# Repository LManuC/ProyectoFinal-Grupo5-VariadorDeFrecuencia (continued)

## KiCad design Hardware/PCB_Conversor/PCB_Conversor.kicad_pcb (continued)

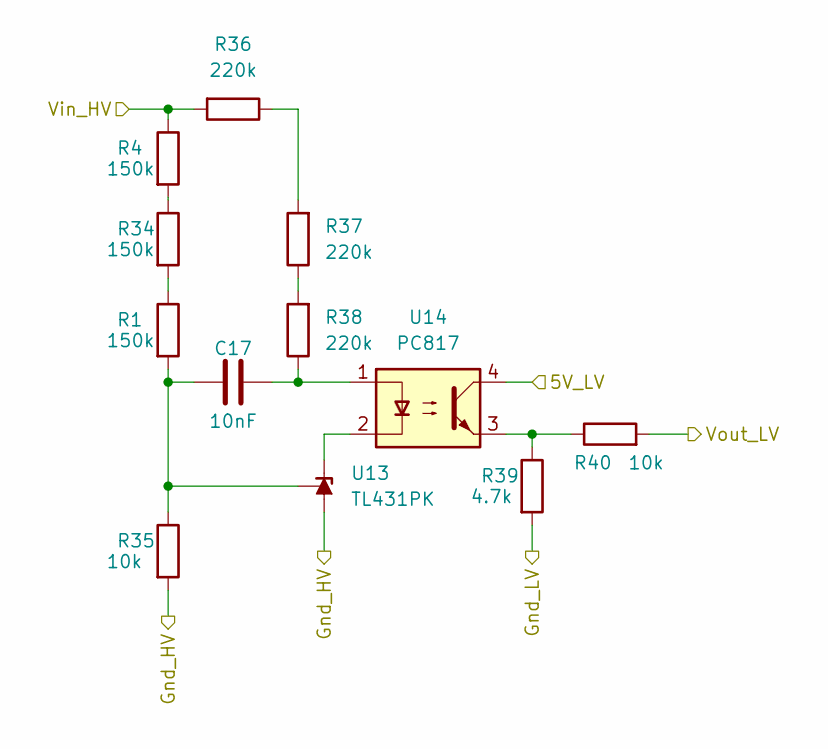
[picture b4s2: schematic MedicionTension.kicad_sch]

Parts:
C17: 10nF; C_0603_1608Metric_Pad1.08x0.95mm_HandSolder
R1, R4, R34: 150k; R_0603_1608Metric_Pad0.98x0.95mm_HandSolder
R35, R40: 10k; R_0603_1608Metric_Pad0.98x0.95mm_HandSolder
R36, R37, R38: 220k; R_0603_1608Metric_Pad0.98x0.95mm_HandSolder
R39: 4.7k; R_0603_1608Metric_Pad0.98x0.95mm_HandSolder
U13: TL431PK; SOT-89-3_Handsoldering
U14: PC817; DIP-4_W7.62mm_SMDSocket_SmallPads

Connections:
/Conversor/Gnd_Inv: R35.2, U13.2 (A); also elsewhere on the board
GND_Cnv: R39.2; also elsewhere on the board
unnamed: C17.2, R38.1, U14.1
unnamed: R1.1, R34.2
unnamed: R4.2, R34.1
unnamed: R36.1, R37.2
unnamed: R37.1, R38.2
unnamed: R39.1, R40.1, U14.3
unnamed: U13.3 (K), U14.2
unnamed: C17.1, R1.2, R35.1, U13.1 (REF)
V_HVBus: R4.1, R36.2; also elsewhere on the board
Vref_5V: U14.4; also elsewhere on the board
Vsens_HVDCBus: R40.2; also elsewhere on the board

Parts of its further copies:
C18: 10nF; C_0603_1608Metric_Pad1.08x0.95mm_HandSolder
R3, R5, R41: 150k; R_0603_1608Metric_Pad0.98x0.95mm_HandSolder
R42, R47: 10k; R_0603_1608Metric_Pad0.98x0.95mm_HandSolder
R43, R44, R45: 220k; R_0603_1608Metric_Pad0.98x0.95mm_HandSolder
R46: 4.7k; R_0603_1608Metric_Pad0.98x0.95mm_HandSolder
U15: TL431PK; SOT-89-3_Handsoldering
U16: PC817; DIP-4_W7.62mm_SMDSocket_SmallPads

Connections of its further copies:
3V3_HMI: U16.4; also elsewhere on the board
/Conversor/Gnd_Inv: R42.2, U15.2 (A); also elsewhere on the board
GND_Cnv: R46.2; also elsewhere on the board
unnamed: C18.2, R45.1, U16.1
unnamed: R3.1, R41.2
unnamed: R5.2, R41.1
unnamed: R43.1, R44.2
unnamed: R44.1, R45.2
unnamed: R46.1, R47.1, U16.3
unnamed: U15.3 (K), U16.2
unnamed: C18.1, R3.2, R42.1, U15.1 (REF)
V_HVBus: R5.1, R43.2; also elsewhere on the board
Vsens_HV_HMI: R47.2; also elsewhere on the board

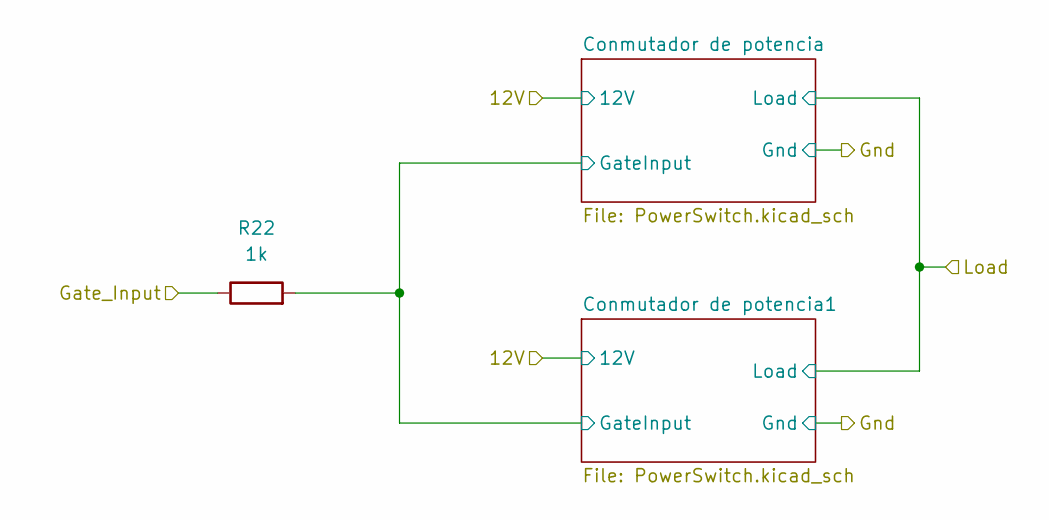
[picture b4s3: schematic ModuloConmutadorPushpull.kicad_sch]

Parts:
R22: 1k; R_0603_1608Metric_Pad0.98x0.95mm_HandSolder

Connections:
/Conversor/Modulo conmutador pushpull/Conmutador de potencia/GateInput: R22.2; also elsewhere on the board
Gate_Input_B: R22.1; also elsewhere on the board

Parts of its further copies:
R24: 1k; R_0603_1608Metric_Pad0.98x0.95mm_HandSolder

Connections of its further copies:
/Conversor/Modulo conmutador pushpull1/Conmutador de potencia/GateInput: R24.2; also elsewhere on the board
Gate_Input_A: R24.1; also elsewhere on the board

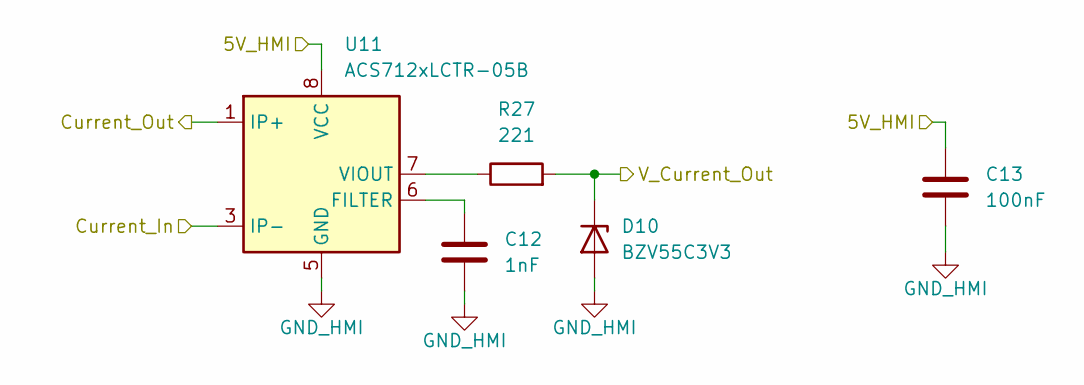
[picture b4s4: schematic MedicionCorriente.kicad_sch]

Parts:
C12: 1nF; C_0603_1608Metric_Pad1.08x0.95mm_HandSolder
C13: 100nF; C_0603_1608Metric_Pad1.08x0.95mm_HandSolder
D10: BZV55C3V3; D_MiniMELF_Handsoldering
R27: 221; R_0603_1608Metric_Pad0.98x0.95mm_HandSolder
U11: ACS712xLCTR-05B; SOIC-8_3.9x4.9mm_P1.27mm

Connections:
5V_HMI: C13.1, U11.8 (VCC); also elsewhere on the board
/Conversor/Medición corriente/Current_In: U11.3 (IP-), U11.4 (IP-); also elsewhere on the board
GND_HMI: C12.2, C13.2, D10.2 (A), U11.5 (GND); also elsewhere on the board
unnamed: C12.1, U11.6 (FILTER)
unnamed: R27.1, U11.7 (VIOUT)
VSens_Corriente: D10.1 (K), R27.2; also elsewhere on the board
V_HVBus: U11.1 (IP+), U11.2 (IP+); also elsewhere on the board

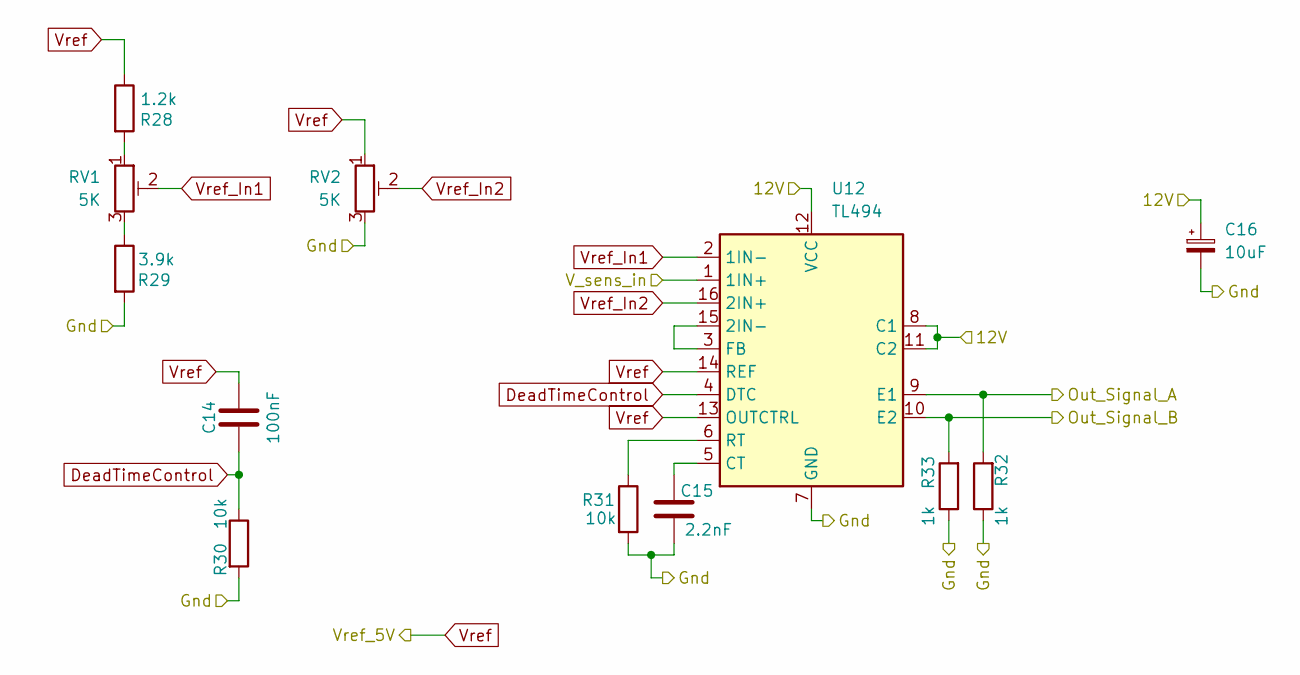
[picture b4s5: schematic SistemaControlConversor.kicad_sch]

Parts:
C14: 100nF; C_0603_1608Metric_Pad1.08x0.95mm_HandSolder
C15: 2.2nF; C_0603_1608Metric_Pad1.08x0.95mm_HandSolder
C16: 10uF; CP_Elec_4x5.4
R28: 1.2k; R_0603_1608Metric_Pad0.98x0.95mm_HandSolder
R29: 3.9k; R_0603_1608Metric_Pad0.98x0.95mm_HandSolder
R30, R31: 10k; R_0603_1608Metric_Pad0.98x0.95mm_HandSolder
R32, R33: 1k; R_0603_1608Metric_Pad0.98x0.95mm_HandSolder
RV1, RV2: 5K; Potentiometer_Bourns_3314S_Horizontal
U12: TL494; SOIC-16_3.9x9.9mm_P1.27mm

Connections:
12V_Cnv: C16.1, U12.8 (C1), U12.11 (C2), U12.12 (VCC); also elsewhere on the board
DeadTimeControl: C14.1, R30.1, U12.4 (DTC)
GND_Cnv: C15.1, C16.2, R29.2, R30.2, R31.2, R32.1, R33.1, RV2.3, U12.7 (GND); also elsewhere on the board
Gate_Input_A: R32.2, U12.9 (E1); also elsewhere on the board
Gate_Input_B: R33.2, U12.10 (E2); also elsewhere on the board
unnamed: R28.2, RV1.1
unnamed: R29.1, RV1.3
unnamed: U12.3 (FB), U12.15 (2IN-)
unnamed: C15.2, U12.5 (CT)
unnamed: R31.1, U12.6 (RT)
Vref_5V: C14.2, R28.1, RV2.1, U12.13 (OUTCTRL), U12.14 (REF); also elsewhere on the board
Vref_In1: RV1.2, U12.2 (1IN-)
Vref_In2: RV2.2, U12.16 (2IN+)
Vsens_HVDCBus: U12.1 (1IN+); also elsewhere on the board

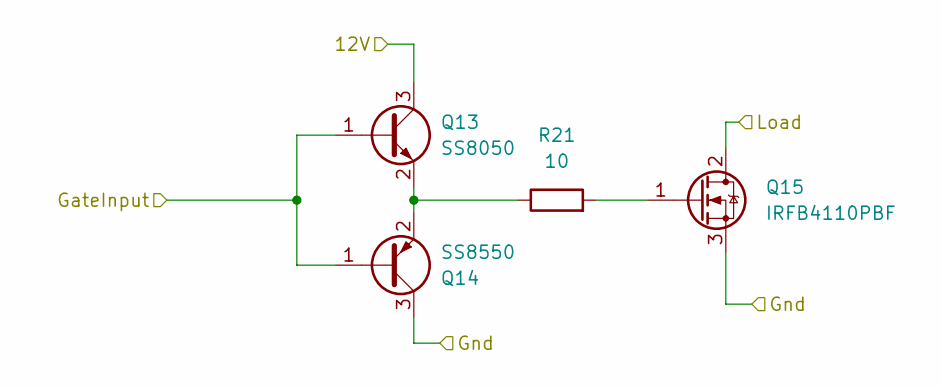
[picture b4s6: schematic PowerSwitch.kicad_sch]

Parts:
Q13: SS8050; SOT-23
Q14: SS8550; SOT-23
Q15: IRFB4110PBF; TO-220-3_Horizontal_TabUp
R21: 10; R_0603_1608Metric_Pad0.98x0.95mm_HandSolder

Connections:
12V_Cnv: Q13.3 (C); also elsewhere on the board
/Conversor/Modulo conmutador pushpull/Conmutador de potencia/GateInput: Q13.1 (B), Q14.1 (B); also elsewhere on the board
/Conversor/Modulo conmutador pushpull/Load: Q15.2 (D); also elsewhere on the board
GND_Cnv: Q14.3 (C), Q15.3 (S); also elsewhere on the board
unnamed: Q13.2 (E), Q14.2 (E), R21.1
unnamed: Q15.1 (G), R21.2

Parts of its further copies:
Q16, Q19, Q22: SS8050; SOT-23
Q17, Q20, Q23: SS8550; SOT-23
Q18, Q21, Q24: IRFB4110PBF; TO-220-3_Horizontal_TabUp
R23, R25, R26: 10; R_0603_1608Metric_Pad0.98x0.95mm_HandSolder

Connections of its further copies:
12V_Cnv: Q16.3 (C), Q19.3 (C), Q22.3 (C); also elsewhere on the board
/Conversor/Modulo conmutador pushpull1/Conmutador de potencia/GateInput: Q19.1 (B), Q20.1 (B), Q22.1 (B), Q23.1 (B); also elsewhere on the board
/Conversor/Modulo conmutador pushpull1/Load: Q21.2 (D), Q24.2 (D); also elsewhere on the board
/Conversor/Modulo conmutador pushpull/Conmutador de potencia/GateInput: Q16.1 (B), Q17.1 (B); also elsewhere on the board
/Conversor/Modulo conmutador pushpull/Load: Q18.2 (D); also elsewhere on the board
GND_Cnv: Q17.3 (C), Q18.3 (S), Q20.3 (C), Q21.3 (S), Q23.3 (C), Q24.3 (S); also elsewhere on the board
unnamed: Q16.2 (E), Q17.2 (E), R23.1
unnamed: Q18.1 (G), R23.2
unnamed: Q19.2 (E), Q20.2 (E), R25.1
unnamed: Q21.1 (G), R25.2
unnamed: Q22.2 (E), Q23.2 (E), R26.1
unnamed: Q24.1 (G), R26.2

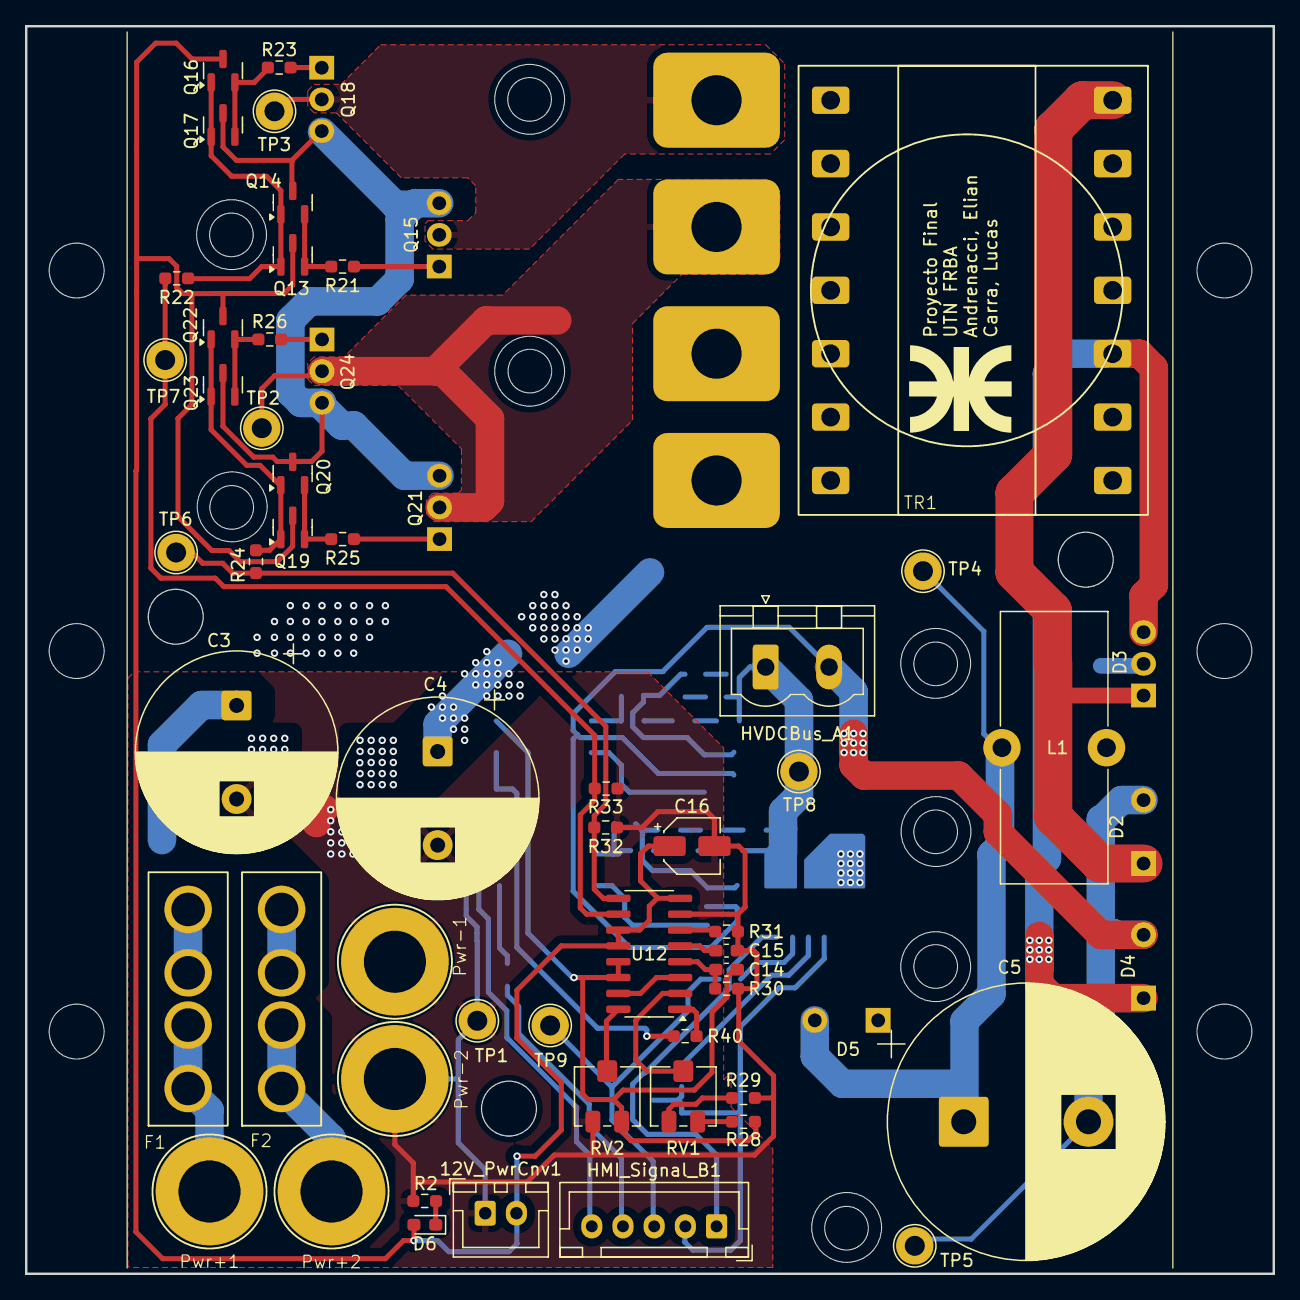
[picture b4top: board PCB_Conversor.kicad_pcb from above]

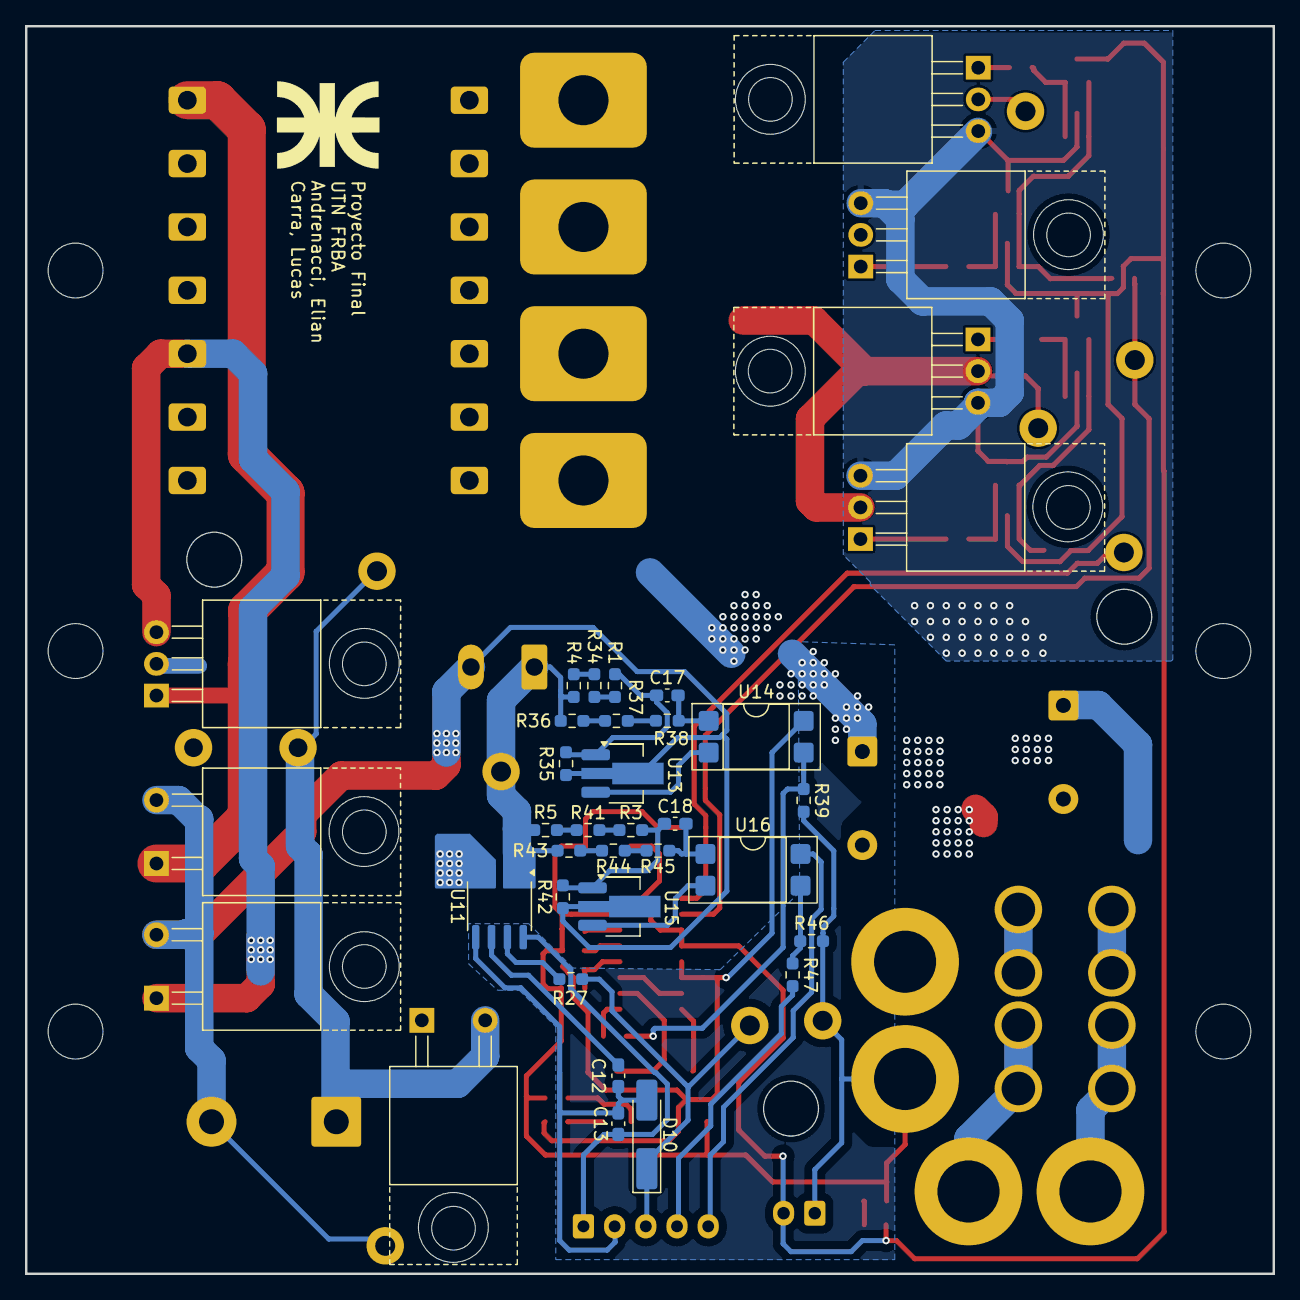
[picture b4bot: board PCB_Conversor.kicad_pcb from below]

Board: 2 copper layers, 100.0 x 100.0 mm, 88 parts (36 on the bottom side), 61 nets.

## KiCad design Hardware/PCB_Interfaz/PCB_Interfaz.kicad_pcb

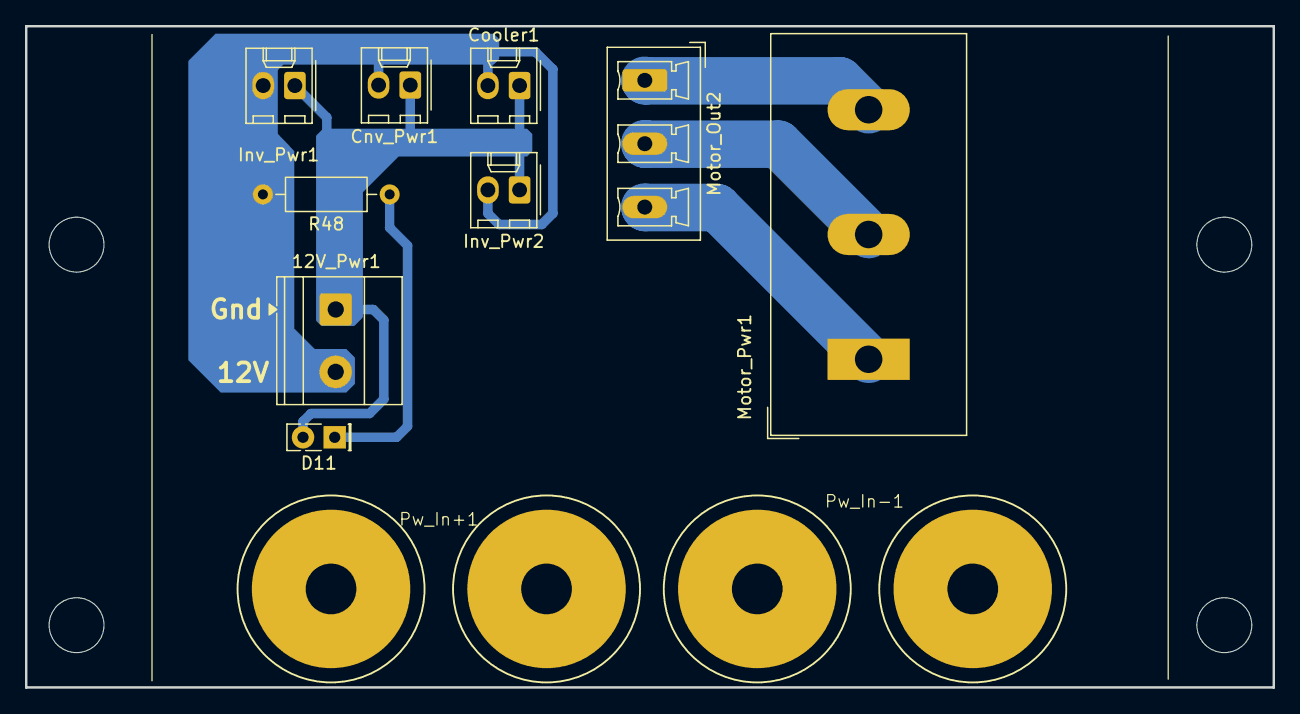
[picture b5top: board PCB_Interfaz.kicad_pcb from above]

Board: 2 copper layers, 100.0 x 53.0 mm, 11 parts (0 on the bottom side), 6 nets.

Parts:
12V_Pwr1: Screw_Terminal_01x02; TerminalBlock_Phoenix_MKDS-1,5-2_1x02_P5.00mm_Horizontal
Cnv_Pwr1: Conn_01x02; Molex_KK-254_AE-6410-02A_1x02_P2.54mm_Vertical
Cooler1: Conn_01x02; Molex_KK-254_AE-6410-02A_1x02_P2.54mm_Vertical
D11: LED_Green; LED_Rectangular_W5.0mm_H2.0mm
Inv_Pwr1, Inv_Pwr2: Conn_01x02; Molex_KK-254_AE-6410-02A_1x02_P2.54mm_Vertical
Motor_Out2: Conn_01x03; PhoenixContact_MCV_1,5_3-G-5.08_1x03_P5.08mm_Vertical
Motor_Pwr1: Screw_Terminal_01x03; TerminalBlock_Dinkle_DT-55-B01X-03_P10.00mm
Pw_In+1: Conn_01x02; BananaSocket - 2P - 4mm
Pw_In-1: Conn_01x02; BananaSocket - 2P - 4mm
R48: 1.2k; R_Axial_DIN0207_L6.3mm_D2.5mm_P10.16mm_Horizontal

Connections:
/Interfaz de conexión/12V_Cnv: 12V_Pwr1.1, Cnv_Pwr1.1, Cooler1.1, D11.2 (A), Inv_Pwr1.1, Inv_Pwr2.1
/Interfaz de conexión/Gnd_Cnv: 12V_Pwr1.2, Cnv_Pwr1.2, Cooler1.2, Inv_Pwr1.2, Inv_Pwr2.2, R48.2
unnamed: D11.1 (K), R48.1
unnamed: Motor_Out2.1, Motor_Pwr1.3
unnamed: Motor_Out2.2, Motor_Pwr1.2
unnamed: Motor_Out2.3, Motor_Pwr1.1

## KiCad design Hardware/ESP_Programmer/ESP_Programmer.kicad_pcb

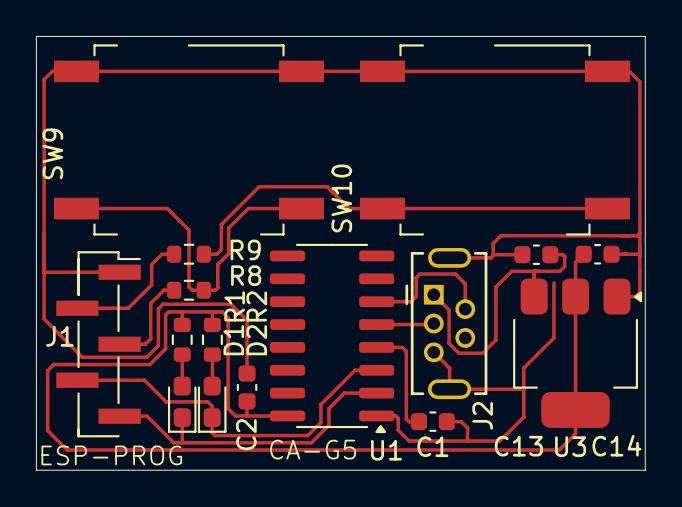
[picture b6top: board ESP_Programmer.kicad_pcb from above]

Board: 2 copper layers, 33.8 x 24.1 mm, 16 parts (0 on the bottom side), 14 nets.

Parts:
C1, C2: 1nF; C_0603_1608Metric
C13, C14: 1uF; C_0603_1608Metric
D1, D2: LED; LED_0603_1608Metric_Pad1.05x0.95mm_HandSolder
J1: Conn_01x05_Pin; PinHeader_1x05_P2.00mm_Vertical_SMD_Pin1Right
J2: USB_OTG; USB_Mini-B_Tensility_54-00023_Vertical
R1, R2, R8, R9: 221; R_0603_1608Metric
SW9, SW10: SW_MEC_5E; SW_MEC_5GSH9
U1: CH340C; SOIC-16_3.9x9.9mm_P1.27mm
U3: AMS1117-3.3; SOT-223-3_TabPin2

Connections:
+3.3V: C2.1, C14.1, R1.1, R2.1, U1.16 (VCC), U3.2 (VO)
+5V: C13.1, J2.1 (VBUS), U3.3 (VI)
/BOOT_prog: J1.2, R9.1
/ENABLE: J1.3, R8.1
/Rx: D2.1 (K), J1.4, U1.3 (RXD)
/Tx: D1.1 (K), J1.5, U1.2 (TXD)
GND: C1.1, C2.2, C13.2, C14.2, J1.1, J2.5 (GND), J2.6 (Shield), SW9.1, SW9.2, SW10.1, SW10.2, U1.1 (GND), U3.1 (GND)
unnamed: D1.2 (A), R1.2
unnamed: D2.2 (A), R2.2
unnamed: J2.3 (D+), U1.5 (UD+)
unnamed: J2.2 (D-), U1.6 (UD-)
unnamed: R8.2, SW9.3 (K), SW9.4 (A)
unnamed: R9.2, SW10.3 (K), SW10.4 (A)
unnamed: C1.2, U1.4 (V3)

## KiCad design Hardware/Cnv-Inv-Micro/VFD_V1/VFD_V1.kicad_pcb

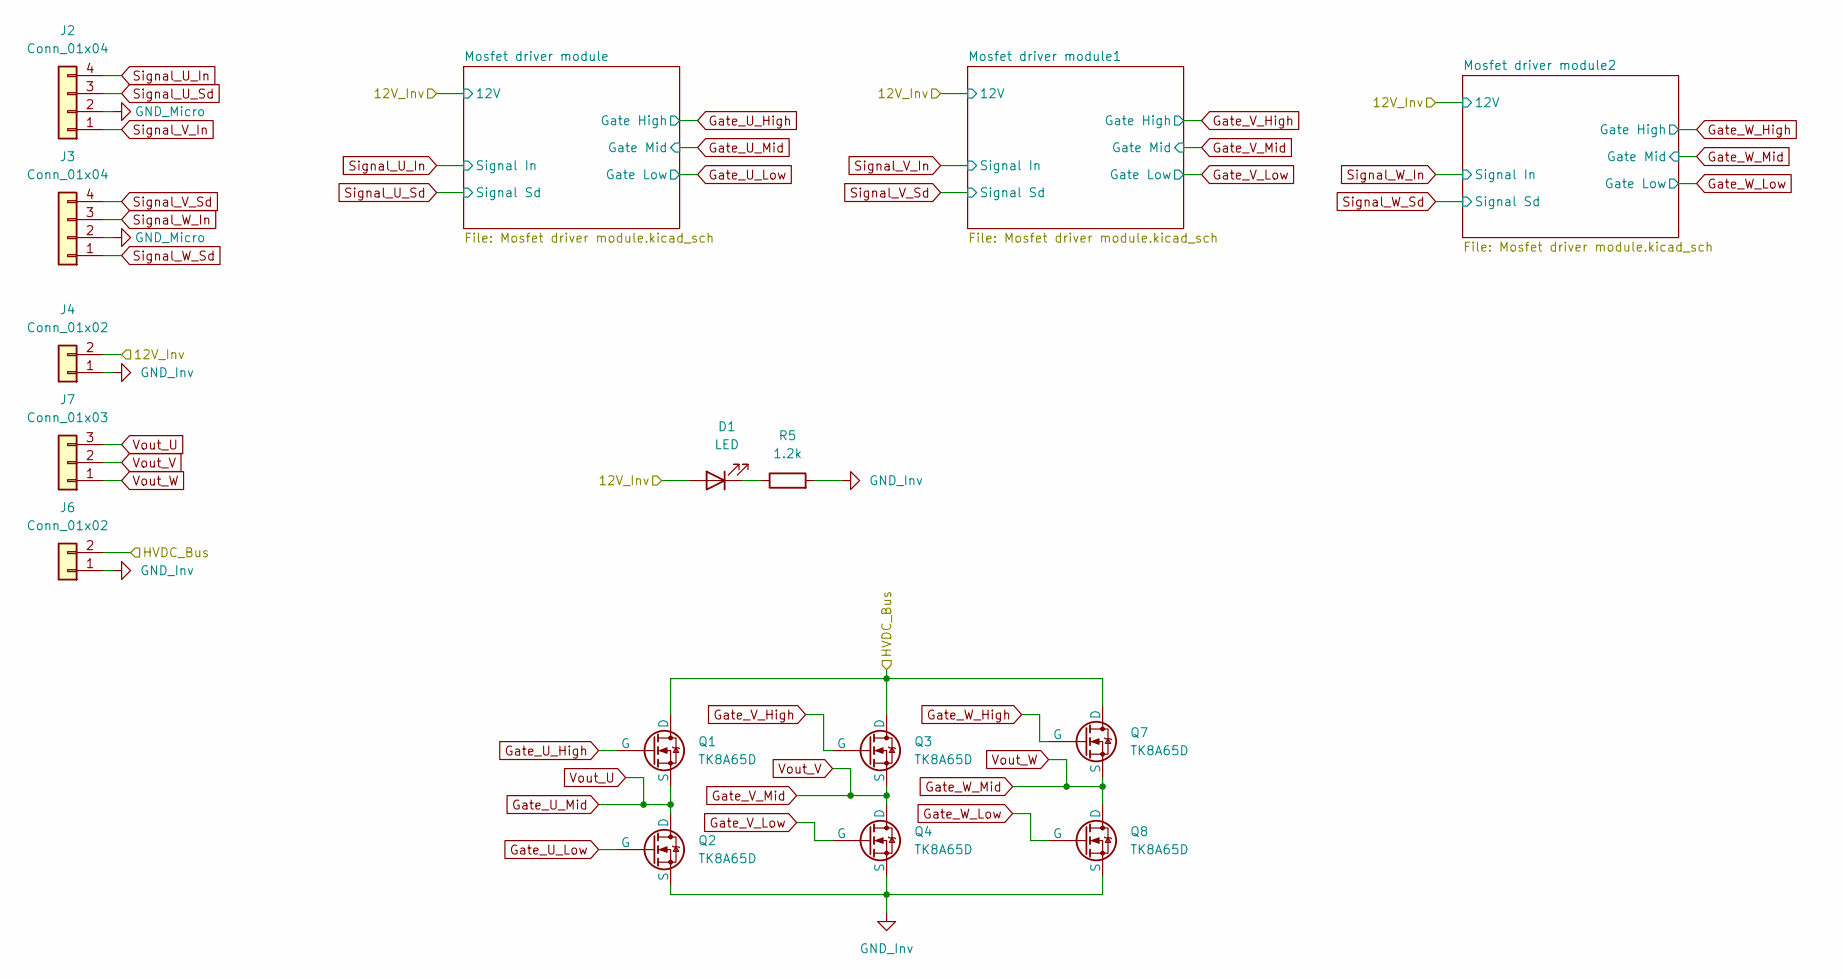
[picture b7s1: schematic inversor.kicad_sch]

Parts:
D1: LED; LED_0603_1608Metric_Pad1.05x0.95mm_HandSolder
J2, J3: Conn_01x04; Molex_KK-254_AE-6410-04A_1x04_P2.54mm_Vertical
J4: Conn_01x02; Molex_KK-254_AE-6410-02A_1x02_P2.54mm_Vertical
J6: Conn_01x02; PhoenixContact_MSTBVA_2,5_2-G-5,08_1x02_P5.08mm_Vertical
J7: Conn_01x03; PhoenixContact_MCV_1,5_3-G-5.08_1x03_P5.08mm_Vertical
Q1, Q2, Q3, Q4, Q7, Q8: TK8A65D; TO-220-3_Horizontal_TabUp
R5: 1.2k; R_0603_1608Metric_Pad0.98x0.95mm_HandSolder

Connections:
/Inversor/12V_Inv: D1.2 (A), J4.2; also elsewhere on the board
/Inversor/HVDC_Bus: J6.2, Q1.2 (D), Q3.2 (D), Q7.2 (D)
GND_Inv: J4.1, J6.1, Q2.3 (S), Q4.3 (S), Q8.3 (S), R5.2; also elsewhere on the board
GND_Micro: J2.2, J3.2; also elsewhere on the board
Gate_U_High: Q1.1 (G); also elsewhere on the board
Gate_U_Low: Q2.1 (G); also elsewhere on the board
Gate_U_Mid: J7.3, Q1.3 (S), Q2.2 (D); also elsewhere on the board
Gate_V_High: Q3.1 (G); also elsewhere on the board
Gate_V_Low: Q4.1 (G); also elsewhere on the board
Gate_V_Mid: J7.2, Q3.3 (S), Q4.2 (D); also elsewhere on the board
Gate_W_High: Q7.1 (G); also elsewhere on the board
Gate_W_Low: Q8.1 (G); also elsewhere on the board
Gate_W_Mid: J7.1, Q7.3 (S), Q8.2 (D); also elsewhere on the board
unnamed: D1.1 (K), R5.1
Signal_U_In: J2.4; also elsewhere on the board
Signal_U_Sd: J2.3; also elsewhere on the board
Signal_V_In: J2.1; also elsewhere on the board
Signal_V_Sd: J3.4; also elsewhere on the board
Signal_W_In: J3.3; also elsewhere on the board
Signal_W_Sd: J3.1; also elsewhere on the board

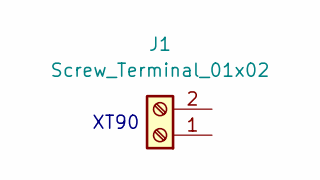
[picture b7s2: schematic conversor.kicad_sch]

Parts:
J1: Screw_Terminal_01x02

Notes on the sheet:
XT90

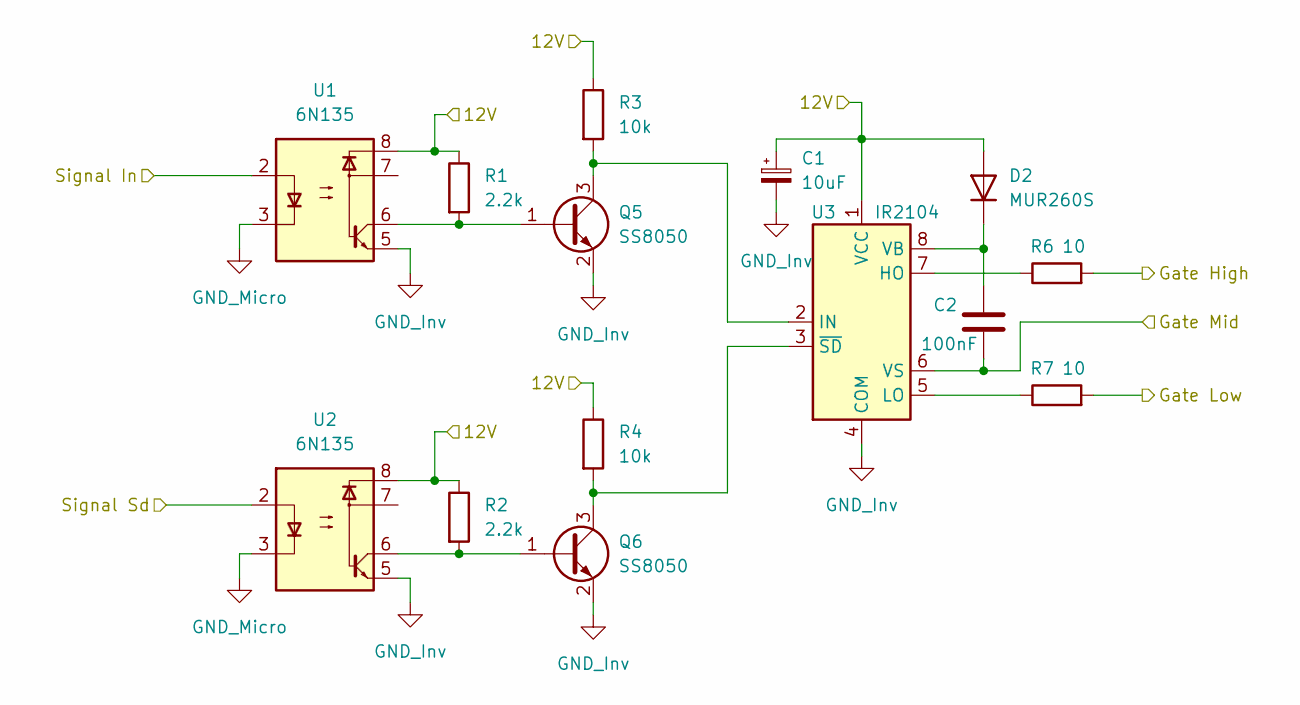
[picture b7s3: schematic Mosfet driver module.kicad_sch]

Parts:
C1: 10uF; CP_Elec_4x5.4
C2: 100nF; C_0603_1608Metric_Pad1.08x0.95mm_HandSolder
D2: MUR260S; D_SMB_Handsoldering
Q5, Q6: SS8050; SOT-23
R1, R2: 2.2k; R_0603_1608Metric_Pad0.98x0.95mm_HandSolder
R3, R4: 10k; R_0603_1608Metric_Pad0.98x0.95mm_HandSolder
R6, R7: 10; R_0603_1608Metric_Pad0.98x0.95mm_HandSolder
U1, U2: 6N135; SOP-8_6.62x9.15mm_P2.54mm
U3: IR2104; SOIC-8_3.9x4.9mm_P1.27mm

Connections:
/Inversor/12V_Inv: C1.1, D2.2 (A), R1.1, R2.1, R3.1, R4.1, U1.8, U2.8, U3.1 (VCC); also elsewhere on the board
GND_Inv: C1.2, Q5.2 (E), Q6.2 (E), U1.5, U2.5, U3.4 (COM); also elsewhere on the board
GND_Micro: U1.3, U2.3; also elsewhere on the board
Gate_U_High: R6.2; also elsewhere on the board
Gate_U_Low: R7.2; also elsewhere on the board
Gate_U_Mid: C2.2, U3.6 (VS); also elsewhere on the board
unnamed: C2.1, D2.1 (K), U3.8 (VB)
unnamed: Q5.1 (B), R1.2, U1.6
unnamed: Q5.3 (C), R3.2, U3.2 (IN)
unnamed: Q6.1 (B), R2.2, U2.6
unnamed: Q6.3 (C), R4.2, U3.3 (~SD)
unnamed: R6.1, U3.7 (HO)
unnamed: R7.1, U3.5 (LO)
Signal_U_In: U1.2; also elsewhere on the board
Signal_U_Sd: U2.2; also elsewhere on the board

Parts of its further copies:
C3, C5: 10uF; CP_Elec_4x5.4
C4, C6: 100nF; C_0603_1608Metric_Pad1.08x0.95mm_HandSolder
D3, D4: MUR260S; D_SMB_Handsoldering
Q9, Q10, Q11, Q12: SS8050; SOT-23
R8, R9, R14, R15: 2.2k; R_0603_1608Metric_Pad0.98x0.95mm_HandSolder
R10, R11, R16, R17: 10k; R_0603_1608Metric_Pad0.98x0.95mm_HandSolder
R12, R13, R18, R19: 10; R_0603_1608Metric_Pad0.98x0.95mm_HandSolder
U4, U5, U7, U8: 6N135; SOP-8_6.62x9.15mm_P2.54mm
U6, U9: IR2104; SOIC-8_3.9x4.9mm_P1.27mm

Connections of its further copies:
/Inversor/12V_Inv: C3.1, C5.1, D3.2 (A), D4.2 (A), R8.1, R9.1, R10.1, R11.1, R14.1, R15.1, R16.1, R17.1, U4.8, U5.8, U6.1 (VCC), U7.8, U8.8, U9.1 (VCC); also elsewhere on the board
GND_Inv: C3.2, C5.2, Q9.2 (E), Q10.2 (E), Q11.2 (E), Q12.2 (E), U4.5, U5.5, U6.4 (COM), U7.5, U8.5, U9.4 (COM); also elsewhere on the board
GND_Micro: U4.3, U5.3, U7.3, U8.3; also elsewhere on the board
Gate_V_High: R12.2; also elsewhere on the board
Gate_V_Low: R13.2; also elsewhere on the board
Gate_V_Mid: C4.2, U6.6 (VS); also elsewhere on the board
Gate_W_High: R18.2; also elsewhere on the board
Gate_W_Low: R19.2; also elsewhere on the board
Gate_W_Mid: C6.2, U9.6 (VS); also elsewhere on the board
unnamed: C4.1, D3.1 (K), U6.8 (VB)
unnamed: C6.1, D4.1 (K), U9.8 (VB)
unnamed: Q9.1 (B), R8.2, U4.6
unnamed: Q9.3 (C), R10.2, U6.2 (IN)
unnamed: Q10.1 (B), R9.2, U5.6
unnamed: Q10.3 (C), R11.2, U6.3 (~SD)
unnamed: Q11.1 (B), R14.2, U7.6
unnamed: Q11.3 (C), R16.2, U9.2 (IN)
unnamed: Q12.1 (B), R15.2, U8.6
unnamed: Q12.3 (C), R17.2, U9.3 (~SD)
unnamed: R12.1, U6.7 (HO)
unnamed: R13.1, U6.5 (LO)
unnamed: R18.1, U9.7 (HO)
unnamed: R19.1, U9.5 (LO)
Signal_V_In: U4.2; also elsewhere on the board
Signal_V_Sd: U5.2; also elsewhere on the board
Signal_W_In: U7.2; also elsewhere on the board
Signal_W_Sd: U8.2; also elsewhere on the board

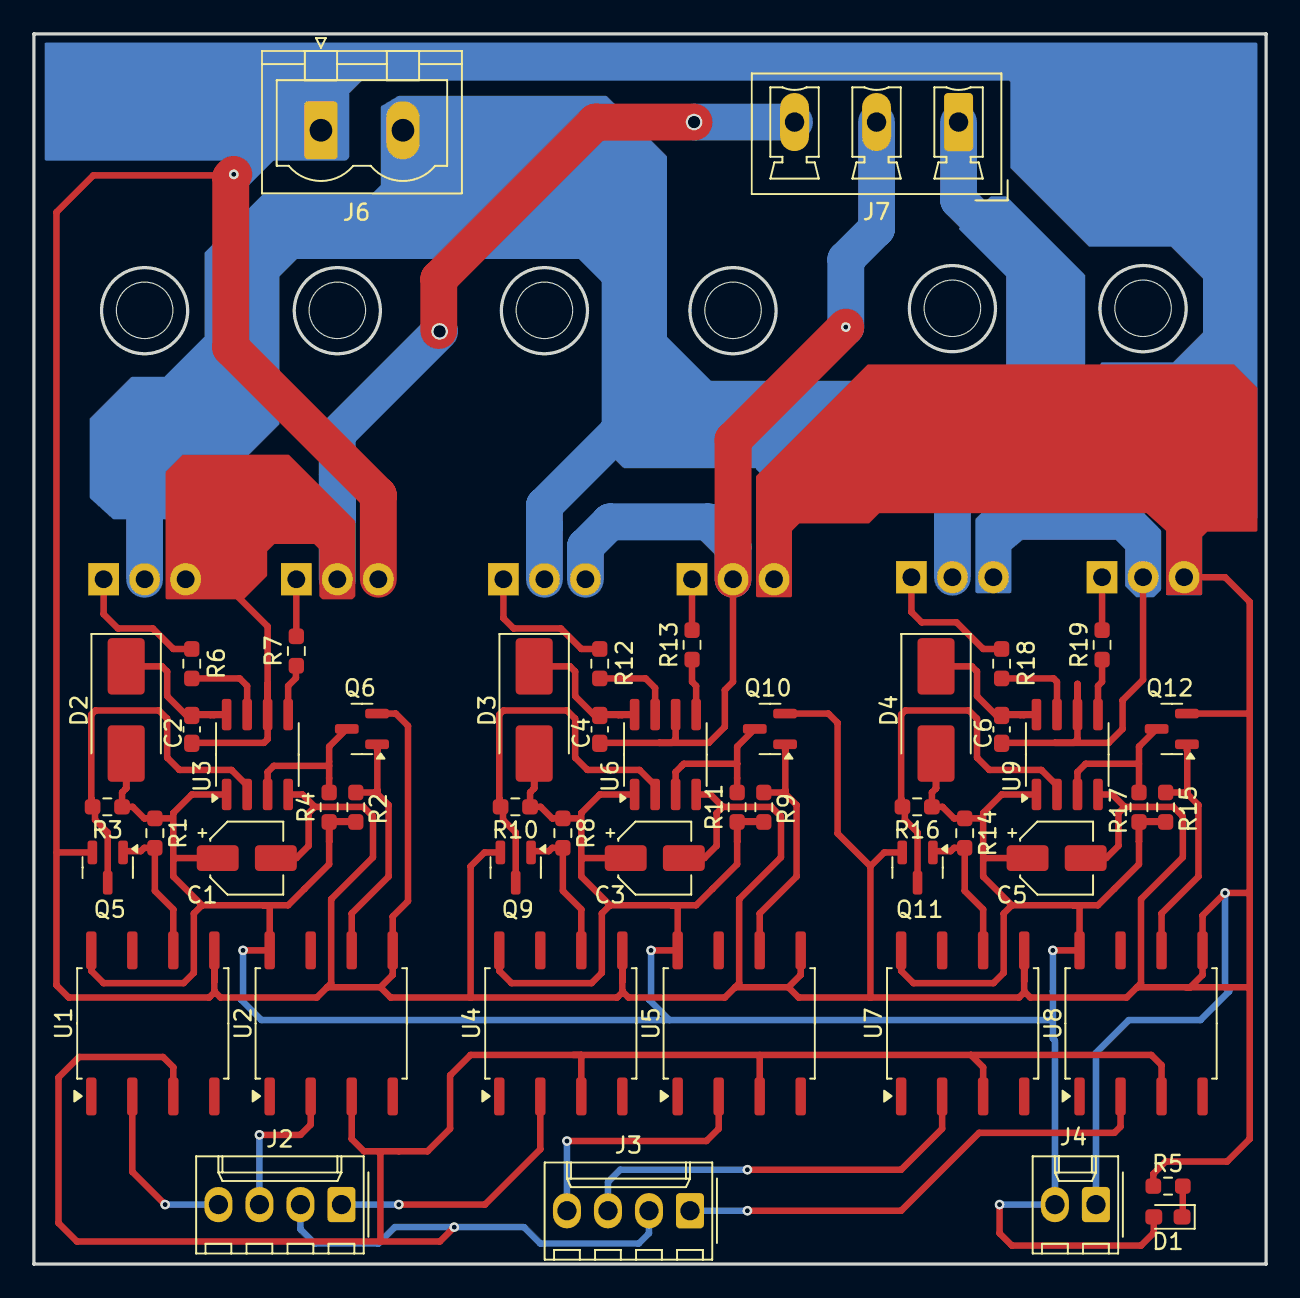
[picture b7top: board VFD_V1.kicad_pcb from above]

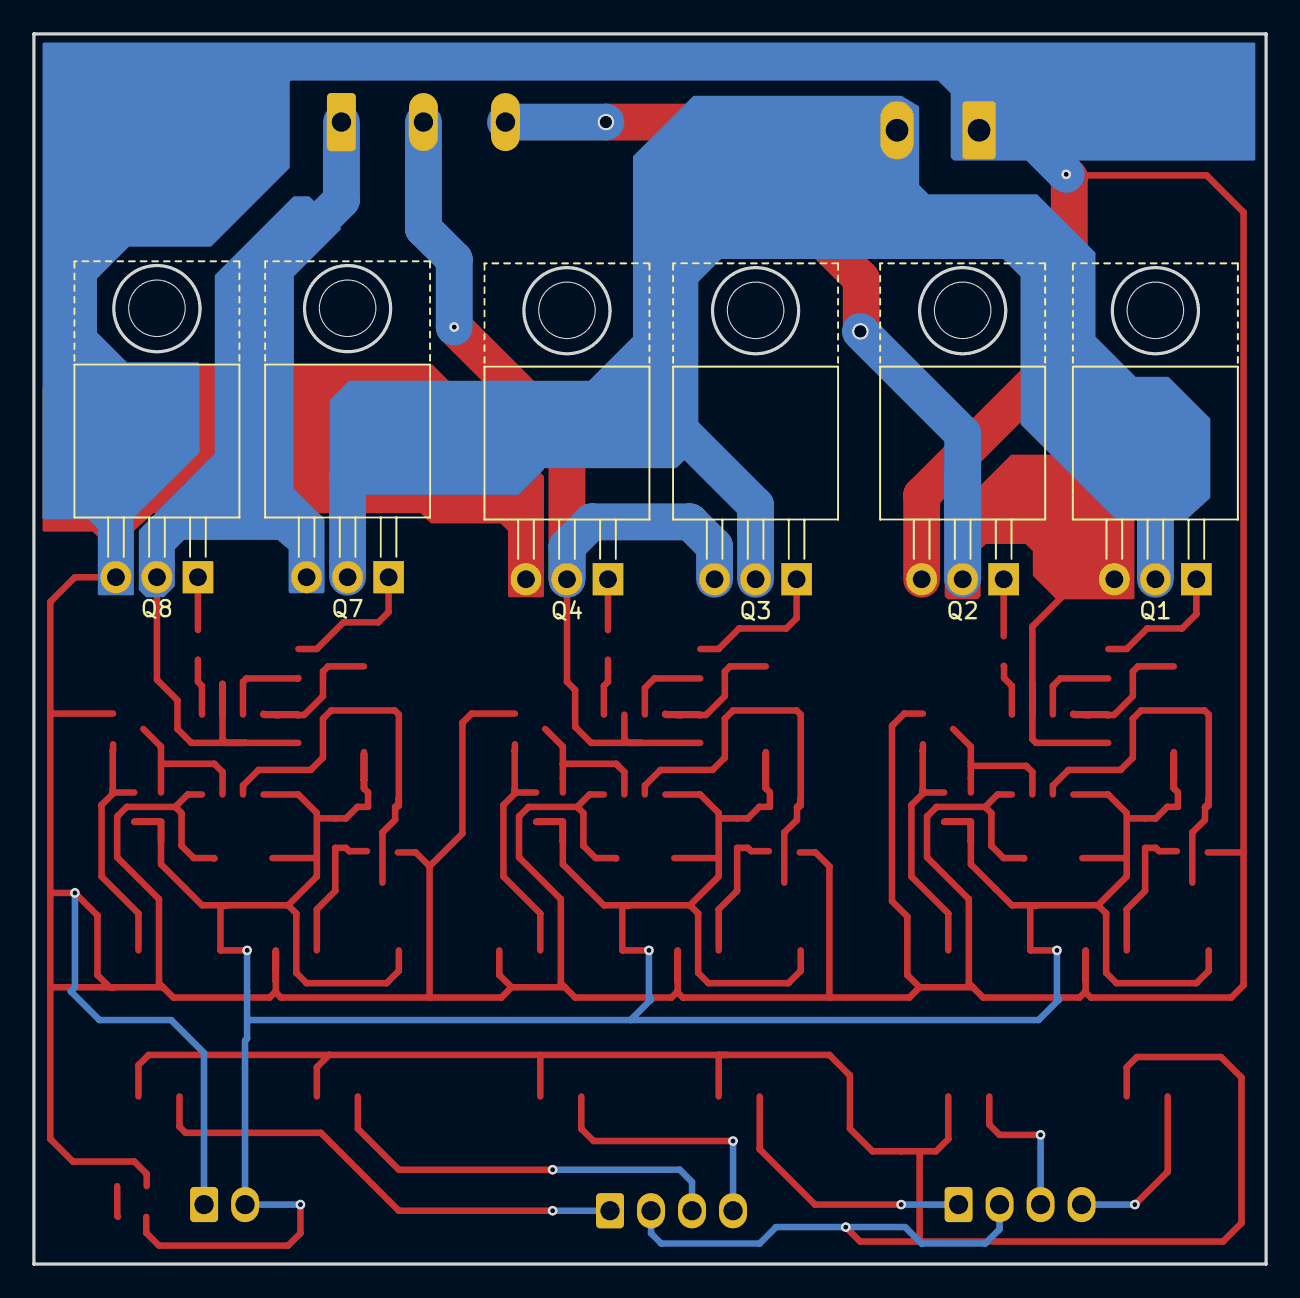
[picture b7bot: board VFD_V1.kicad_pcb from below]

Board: 2 copper layers, 76.3 x 76.2 mm, 55 parts (6 on the bottom side), 41 nets.
